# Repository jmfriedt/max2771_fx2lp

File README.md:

## MAX2771 multiband GNSS receiver for FX2LP

See [this movie](https://www.youtube.com/watch?v=B5UcFnkbXIk) to assess what the result of this
investigation might be. Many more GNSS bands and processing schemes are available with the very
flexible SDR reception platform. The use and results from the software in this repository
are featured in the French magazine <a href="https://connect.ed-diamond.com/hackable/hk-057/programmation-usb-sous-gnu-linux-application-du-fx2lp-pour-un-recepteur-de-radio-logicielle-dedie-aux-signaux-de-navigation-par-satellite-1-2">Hackable</a> (Nov-Dec 2024 and Mar-Apr 2025)

This project was featured on [Hackaday](https://hackaday.com/2024/11/03/gnss-reception-with-clone-sdr-board/)
November 3rd, 2024 and presented at the [2025 FOSDEM](https://www.fosdem.org/2025/schedule/event/fosdem-2025-4150-broadband-data-transfer-over-usb-for-gnu-linux-1-2-ghz-l-band-sdr-receiver-dedicated-to-gnss-and-other-reception-interfacing-with-pocketsdr-gnu-radio-and-gnss-sdr/). The original PocketSDR
<a href="https://www.mdpi.com/2226-4310/12/7/620">has been used</a> for assessing the Lunar Augmented Navigation Service.

### Objective: multi-MAX2771 GNSS receiver with up to 44 MS/s bulk USB communication

... for
* multiband GNSS (or other L-band signal) acquisition and processing if a power combiner 
(e.g. MiniCircuits ZAPD-2DC+) is used to feed both chips with the signal coming from a 
single multiband antenna
* CRPA (Controlled Radiation Pattern Antenna) if each chip is fed from a different
antenna for spatial diversity
* applicable to any L-band communication systems sampled with 2-3 bit ADC (verified with
Iridium)

Assembled daughter board: the missing 24 MHz oscillator is replaced with the 
24 MHz output from one of the resonator pins fitted on the FX2LP board. However,
the frequency pulling by the capacitor leads to a 3 kHz offset (2 ppm) which must
be compensated for when processing (acquisition phase of GNSS signal analysis) the
recorded signals. This feature is however illustrated to emphasize that the GNSS
receiver can be clocked by an external (24 MHz) source, a capability missing from most
commercial GNSS receivers.

Processing relies on the PocketSDR software provided by Tomoji Takasu at
https://github.com/tomojitakasu/PocketSDR.

The firmware for the FX2LP is compiled using opensource tools including the
``sdcc`` compiler, ``fx2lib`` library, ``cycfx2prog`` for prototyping the 8051 embedded
software and  ``fxload`` for flashing the onboard EEPROM.

### Getting started (assuming development on a GNU/Linux system)

1. Compile the FX2LP 8051 firmware (assumes ``sdcc`` is installed):
```
cd FX2LP/fx2lib
make
cd ../complete_fw
make
```
must complete with ``build/complete_fw.ihx`` in ``FX2LP/complete_fw``

2. Compile ``fxload`` for flashing the FX2LP
```
cd fxload
git submodule update --init
cmake .
make -j12
```

3. Flash the firmware in the FX2LP development board: switch on the board with the jumper to the bottom left (with the USB port facing
upward) closed in order to start the bootloader (``lsusb`` must return ``ID 04b4:8613 Cypress Semiconductor Corp. CY7C68013 EZ-USB FX2 
USB 2.0 Development Kit``):
```
sudo ./fxload/src/fxload load_eeprom --device 04b4:8613 --ihex-path ./FX2LP/complete_fw/build/complete_fw.ihx -t FX2LP --control-byte 0xC2 -s ./fxload/resources/Vend_Ax.hex
```
which must reply with
```
FX2:  config = 0x42, disconnected, I2C = 100 KHz
Done.
```

In case a message stating ``WARNING: don't see a large enough EEPROM`` is displayed, then the first byte of the EEPROM must be erased. To do so,
follow the sequences in ``FX2LP/bulk_read_example`` and most significantly the section about *Erase EEPROM and flash program to EEPROM*

4. Check the firmware has been flashed: switch off, remove the bottom-left jumper (to execute the firmware flashed in the EEPROM) and
restart the FX2LP: ``lsusb`` must now indicate ``ID 04b4:1004 Cypress Semiconductor Corp. There``

If so, the FX2LP is ready to communicate with PocketSDR ``app/pocket_conf/pocket_conf`` for configuring the MAX2771 (SPI communication)
or with ``app/pocket_dump/pocket_dump`` for streaming data from the FX2LP to the host computer through a USB Bulk interface.

## Cross compiling PocketSDR with Buildroot

Make sure FFTW with single precision resolution, and libusb are included 
in the Buildroot compilation toolchain.

0. in ``PocketSDR/lib/``: ``./clone_lib.sh`` as would be done on the host
1. in ``PocketSDR/lib/libfec``: 
```
./configure cross_compiling=yes --build=aarch64-buildroot-linux-gnu CC=aarch64-buildroot-linux-gnu-gcc
```
2. in ``PocketSDR/lib/build``, replace all ``CC = gcc`` in all .mk files with
``CC ?= gcc``, remove ``-DAVX2 -mavx2 -mfma`` from ``libsdr.mk``, and 
```
CC=aarch64-linux-gcc make
make install
```
3. in ``PocketSDR_RPi4/app``: edit all ``*/makefile`` and replace ``CC = g..``
with ``CC ?= g..`` (where .. is ``cc`` or ``++``), remove ``-DAVX2 -mavx2 -mfma``
from the ``pocket_snap`` makefile, and in ``makefile`` replace 
all ``make -C`` with ``CC=aarch64-linux-gcc make -C``
4. on a Raspberry Pi, make sure to increase CPU performance:
```
echo "performance" > /sys/devices/system/cpu/cpu0/cpufreq/scaling_governor
```
5. on a Raspberry Pi, make sure to write to a ramfs rather than the slow
SD card (``/tmp`` must be a tmpfs)

```
# ./app/pocket_dump/pocket_dump -t 10 /tmp/1.bin /tmp/2.bin
  TIME(s)    T   CH1(Bytes)   T   CH2(Bytes)   RATE(Ks/s)
     10.0   IQ     79953920  IQ     79953920       3995.3
# lsusb
Bus 001 Device 001: ID 1d6b:0002
Bus 001 Device 003: ID 04b4:1004
Bus 001 Device 002: ID 2109:3431
Bus 002 Device 001: ID 1d6b:0003
# uname -a
Linux buildroot 6.6.28-v8 #1 SMP PREEMPT Mon Feb  3 08:00:06 UTC 2025 aarch64 GNU/Linux
```
and the acqisition is validated on the host (the Raspberry Pi is lacking matplotlib and scipy)
with ``python3 python/pocket_acq.py -f 4  -sig L1CA -prn 1-32 /tmp/2.bin``

### Non-GNSS uses
The L-band is used for many non-GNSS applications. The VCO of the upper-L band receiver was tested
to lock up to 1638 MHz (RDIV=8, NDIV=546), well above Iridium (1616-1626.5 MHz), and down to 1458 MHz 
(RDIV=400, NDIV=24300), unfortunately still too high for the neutral hydrogen line (1420.4 MHz or 
38 MHz away, above the 22 MHz Nyquist frequency when sampling at 44 MS/s, the maximum rate allowed 
by the MAX2771) but compatible with <a href="https://www.youtube.com/watch?v=0UFHMCiM-60">Inmarsat</a>
(1525-1547 MHz).

The MAX2771 is expected to be compatible with receiving NISAR bursts since the 1257.5+/-40 MHz lies 
within the lower L-band VCO tuning range (1160-1290 MHz).

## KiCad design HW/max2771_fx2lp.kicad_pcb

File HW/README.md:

From Tomoji Takasu's Pocket SDR design, v2.3 found at https://github.com/tomojitakasu/PocketSDR, 
to be fitted on https://fr.aliexpress.com/item/1005006134347046.html FX2LP development board:

Schematic:

Notice that the low-pass matching filters L1/C2 and L3/C4 are fitted with 5.6 nH/1.7 pF and
8.4 nH/1.1 pF according to the typical application circuit found on page 49 of the datasheet.
The values are selected for the upper and lower L-band respectively. If both MAX2771 are to be
used in the same band, e.g. for CRPA, then replace the L/C values with the values best suited
for the targeted band.

Board layers (4-layer circuit to match the 50-ohm transmission lines in the L-band):

Use the interactive BOM (in the <a href="bom/">bom/</a> subdirectory) when assembling the board.

Result of the assembled board: configuring both MAX2771 to collect the 
upper (L1) band with 8 MHz sampling rate and 2 MHz IF bandwith
```
sudo ./app/pocket_conf/pocket_conf conf/pocket_L1L1_8MHz.conf
```
and recording using
```
sudo ./app/pocket_dump/pocket_dump -t 5 ch1.bin ch2.bin
```
The two binary files are processed for acquisition of GPS L1 C/A signal with
```
python3 ./python/pocket_acq.py ch2.bin -d 30000 -f 8 -fi 2 -sig L1CA -prn 1-32
```
with the ``-d`` option to reach Doppler shifts up to 30 kHz to account for
the poor quality TCXO whereas the default is to search for 5 kHz (theoretical
Doppler shift maximum assuming a perfect reference clock, e.g. Rb, Cs or HM 
source or good quality OCXO).

First demonstration, Doppler limited to 30 kHz offset from carrier:

Second demonstration, Doppler extended to 40 kHz offset from carrier matching the mobile phone
measurements:

Experimental setup:

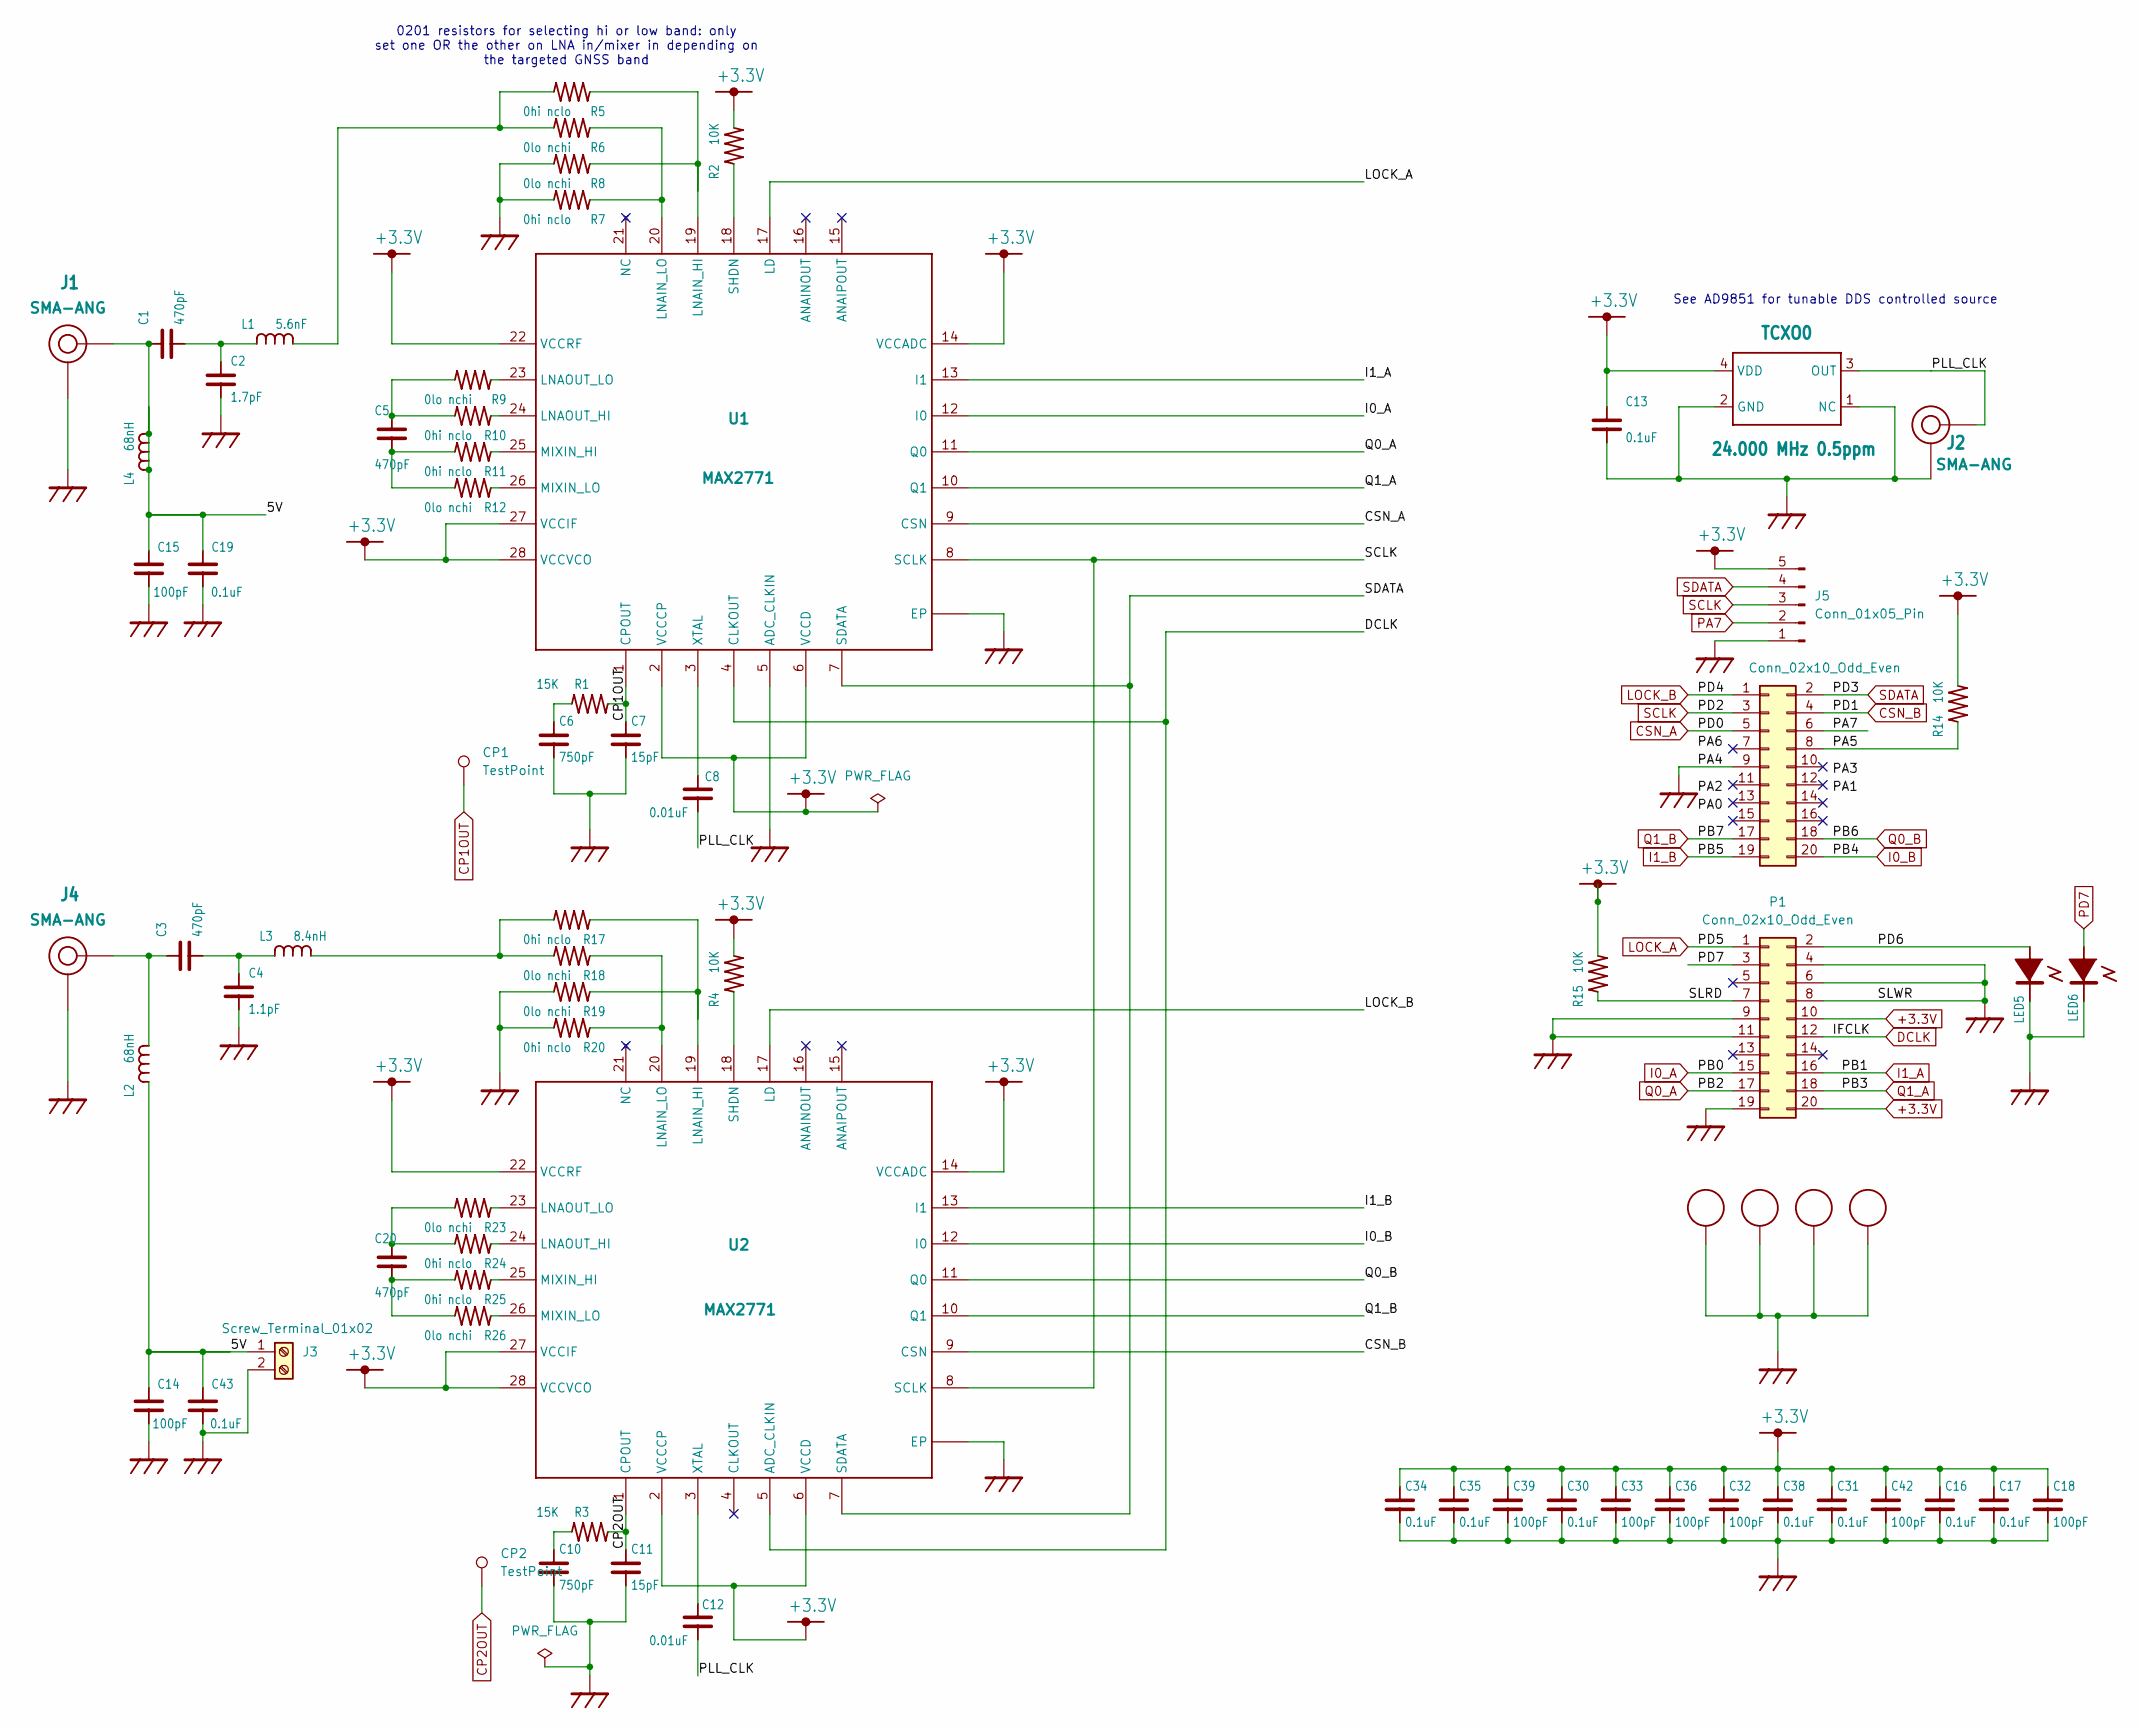
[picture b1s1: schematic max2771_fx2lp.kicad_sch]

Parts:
C1, C3, C5, C20: 470pF; C1005
C2: 1.7pF; C1005
C4: 1.1pF; C1005
C6, C10: 750pF; C1005
C7, C11: 15pF; C1005
C8, C12: 0.01uF; C1005
C13, C16, C17, C19, C30, C31, C34, C35, C38, C43: 0.1uF; C1005
C14, C15, C18, C32, C33, C36, C39, C42: 100pF; C1005
CP1, CP2: TestPoint; TestPoint_Pad_2.0x2.0mm
J1, J2, J4: SMA-ANG
J3: Screw_Terminal_01x02; PinHeader_1x02_P2.54mm_Vertical
J5: Conn_01x05_Pin; PinHeader_1x05_P2.54mm_Vertical
L1: 5.6nF; C1608
L2, L4: 68nH; C1608
L3: 8.4nH; C1608
LED5, LED6: LED1608; LED_1608
P1, P2: Conn_02x10_Odd_Even; PinSocket_2x10_P2.54mm_Vertical
R1, R3: 15K; C1005
R2, R4, R14, R15: 10K; C1005
R5, R7, R10, R11, R17, R20, R24, R25: 0hi nclo; R_0201_0603Metric
R6, R8, R9, R12, R18, R19, R23, R26: 0lo nchi; R_0201_0603Metric
TCXO0: 24.000 MHz 0.5ppm; TCXO
U1, U2: MAX2771; TQFN28

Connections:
+3.3V: C13.1, C16.1, C17.1, C18.1, C30.1, C31.1, C32.1, C33.1, C34.1, C35.1, C36.1, C38.1, C39.1, C42.1, J5.5, P1.10, P1.20, R2.2, R4.2, R14.2, R15.2, TCXO0.4 (VDD), U1.2 (VCCCP), U1.6 (VCCD), U1.14 (VCCADC), U1.22 (VCCRF), U1.27 (VCCIF), U1.28 (VCCVCO), U2.2 (VCCCP), U2.6 (VCCD), U2.14 (VCCADC), U2.22 (VCCRF), U2.27 (VCCIF), U2.28 (VCCVCO)
/PA5: P2.8, R14.1
/PD6: LED5.1 (+), P1.2
/PLL_CLK: C8.1, C12.1, J2.P1 (RF), TCXO0.3 (OUT)
/SLRD: P1.7, R15.1
CP1OUT: C7.1, CP1.1, R1.2, U1.1 (CPOUT)
CP2OUT: C11.1, CP2.1, R3.2, U2.1 (CPOUT)
CPAD_2.2MM: C2.1, C4.2, C6.2, C7.2, C10.2, C11.2, C13.2, C14.1, C15.1, C16.2, C17.2, C18.2, C19.1, C30.2, C31.2, C32.2, C33.2, C34.2, C35.2, C36.2, C38.2, C39.2, C42.2, C43.1, J1.P2 (GND), J1.P3 (GND), J1.P4 (GND), J1.P5 (GND), J2.P2 (GND), J2.P3 (GND), J2.P4 (GND), J2.P5 (GND), J3.2, J4.P2 (GND), J4.P3 (GND), J4.P4 (GND), J4.P5 (GND), J5.1, LED5.2, LED6.2, P1.4, P1.6, P1.8, P1.9, P1.11, P1.19, P2.9, R7.2, R8.2, R19.2, R20.2, TCXO0.1 (NC), TCXO0.2 (GND), U1.5 (ADC_CLKIN), U1.C1 (EP), U1.C2 (EP), U1.C3 (EP), U1.C4 (EP), U1.EP, U1.V1 (EP), U1.V2 (EP), U1.V3 (EP), U1.V4 (EP), U1.V5 (EP), U1.V6 (EP), U1.V7 (EP), U1.V8 (EP), U1.V9 (EP), U2.C1 (EP), U2.C2 (EP), U2.C3 (EP), U2.C4 (EP), U2.EP, U2.V1 (EP), U2.V2 (EP), U2.V3 (EP), U2.V4 (EP), U2.V5 (EP), U2.V6 (EP), U2.V7 (EP), U2.V8 (EP), U2.V9 (EP)
CSN_A: P2.5, U1.9 (CSN)
CSN_B: P2.4, U2.9 (CSN)
DCLK: P1.12, U1.4 (CLKOUT), U2.5 (ADC_CLKIN)
I0_A: P1.15, U1.12 (I0)
I0_B: P2.20, U2.12 (I0)
I1_A: P1.16, U1.13 (I1)
I1_B: P2.19, U2.13 (I1)
LOCK_A: P1.1, U1.17 (LD)
LOCK_B: P2.1, U2.17 (LD)
unnamed: C3.1, J4.P1 (RF), L2.2
unnamed: C1.2, C2.2, L1.1
unnamed: L1.2, R5.2, R6.2
unnamed: C3.2, C4.1, L3.1
unnamed: L3.2, R17.2, R18.2
unnamed: C6.1, R1.1
unnamed: R2.1, U1.18 (SHDN)
unnamed: C10.1, R3.1
unnamed: R4.1, U2.18 (SHDN)
unnamed: R5.1, R8.1, U1.19 (LNAIN_HI)
unnamed: R6.1, R7.1, U1.20 (LNAIN_LO)
unnamed: R9.1, U1.23 (LNAOUT_LO)
unnamed: R10.1, U1.24 (LNAOUT_HI)
unnamed: C5.1, R9.2, R10.2
unnamed: R11.1, U1.25 (MIXIN_HI)
unnamed: C5.2, R11.2, R12.2
unnamed: R12.1, U1.26 (MIXIN_LO)
unnamed: R17.1, R19.1, U2.19 (LNAIN_HI)
unnamed: R18.1, R20.1, U2.20 (LNAIN_LO)
unnamed: R23.1, U2.23 (LNAOUT_LO)
unnamed: C20.1, R23.2, R24.2
unnamed: R24.1, U2.24 (LNAOUT_HI)
unnamed: R25.1, U2.25 (MIXIN_HI)
unnamed: C20.2, R25.2, R26.2
unnamed: R26.1, U2.26 (MIXIN_LO)
unnamed: C8.2, U1.3 (XTAL)
unnamed: C12.2, U2.3 (XTAL)
PA7: J5.2, P2.6
PD7: LED6.1 (+), P1.3
Q0_A: P1.17, U1.11 (Q0)
Q0_B: P2.18, U2.11 (Q0)
Q1_A: P1.18, U1.10 (Q1)
Q1_B: P2.17, U2.10 (Q1)
SCLK: J5.3, P2.3, U1.8 (SCLK), U2.8 (SCLK)
SDATA: J5.4, P2.2, U1.7 (SDATA), U2.7 (SDATA)

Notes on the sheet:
0201 resistors for selecting hi or low band: only set one OR the other on LNA in/mixer in depending on the targeted GNSS band
See AD9851 for tunable DDS controlled source

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
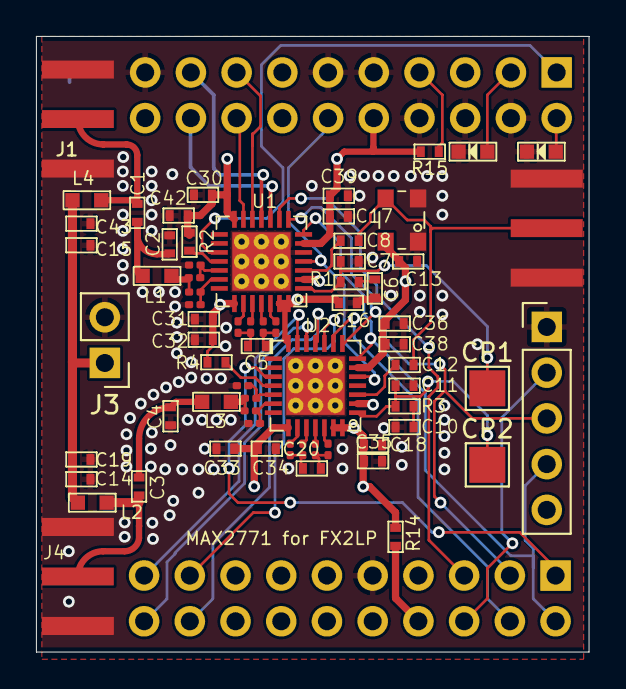
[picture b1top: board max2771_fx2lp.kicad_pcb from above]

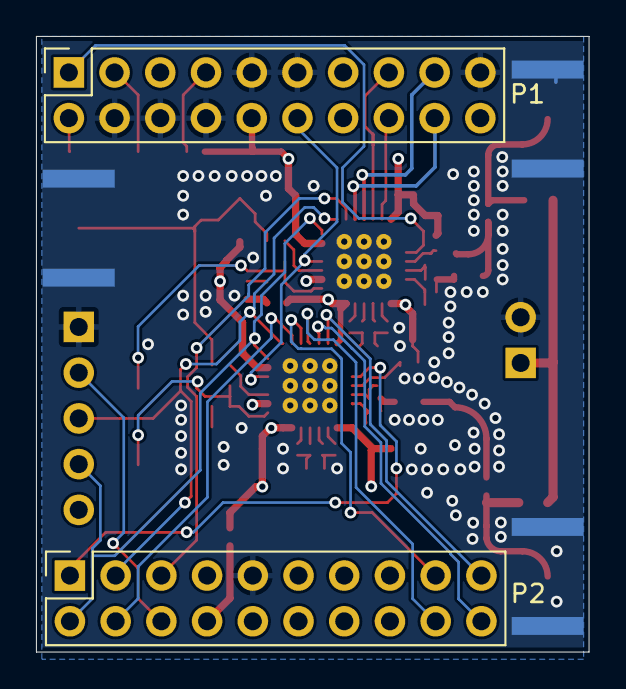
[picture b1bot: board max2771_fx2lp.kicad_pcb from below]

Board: 4 copper layers, 30.7 x 34.2 mm, 70 parts (2 on the bottom side), 54 nets.

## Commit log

2024-06-12 phone screenshot width
2024-06-13 add option for feeding either Hi or Lo frequency band
2024-06-13 sample data
2024-06-13 datasets + SVG
2024-06-14 mirror connectors
2024-06-15 final version sent for fabrication
2024-06-15 iridium band
2024-06-16 iridium signals + GPS squared carriers
2024-06-16 layout
2024-06-16 iridium decoding with gr-iridium
2024-06-16 finalized Iridium with IF
2024-06-22 README under MAX2771 Eval Board
2024-06-30 picture of the assembled board
2024-06-30 blinking LED example
2024-06-30 functional reception demonstration
2024-06-30 more functional example demo, increasedDoppler
2024-07-07 CRPA synchronization and gnss-sdr decoding
2024-07-07 spoofing description
2024-07-07 spoofing: genuine
2024-07-07 more gnss-sdr
2024-07-07 RINEX gnss-sdr
2024-07-09 python access to Vendor requests from PocketSDR firmware
2024-07-10 read/write MAX2771 registers from Python
2024-07-10 basic sdcc/fx2lib example handling Vendor Request messages with SPI bitbang emulation
2024-07-10 SPI management using sdcc and Vendor Request commands
2024-07-11 hardware validation procedure
2024-07-14 Keil vs SDCC endianness issue solved + final firmware with bulk USB communication
2024-07-14 README
2024-07-14 add EEPROM support
2024-07-14 datasheet: register layout
2024-07-14 ADC datarate
2024-07-15 Manually filled buffer bulk transfer example
2024-07-16 bulk transfer example in plain C
2024-07-17 Bulk USB interface read from C and Python, including from EEPROM
2024-07-17 EEPROM jumper
2024-07-29 real time processing and time offset exrtaction
2024-07-29 Allan deviation
2024-07-29 Allan deviation: README
2024-07-29 AD9851: README
2024-07-31 long term dt measurements
2024-07-31 time evolution
2024-08-04 add frequency offset
2024-08-05 first attempt at closed loop analysis
2024-08-05 add dataset
2024-08-06 update documentation/Makefile
2024-08-06 add test program
2024-08-12 AD9851 configuration script
2024-08-14 early init of AD9851
2024-08-19 GPSDO stability
2024-08-19 iridium
2024-08-19 first AD9851 tests
2024-10-05 repeat GPS spoofing detection with dual MAX2771 board
2024-10-21 enable EEPROM read/write
2024-10-21 correct error on eeprom write function
2024-10-21 add safety on EEPROM write
2024-10-21 add python test
2024-10-22 add datasheet reference
2024-10-22 mandatory pin configurations
2024-10-23 check bulk commuication with square wave clock generator
2024-10-23 add vendor request format
2024-10-24 Vendor Request format and handling
2024-10-24 LED polarity
2024-10-25 update READMEs
2024-10-26 move figure
2024-11-04 add translation of Hackable article
2024-11-05 update English translation of Hackable article
2024-12-31 add second article in English
2025-01-04 configuration files for RINEX differences
2025-01-04 Channels
2025-01-04 remove unnecessary config line
2025-01-08 RINEX pseudo-range difference
2025-01-08 fine delay measurement
2025-01-09 delay difference measurement
2025-01-09 update register 0 and register1 default values
2025-01-11 complex baseband measurements
2025-01-18 change VID/PID to allow multiple boards to be used simultaneously
2025-01-18 document pocket_scan usage
2025-01-25 real time display in GNU Radio
2025-01-31 decode packed 8 bits with GNU Radio
2025-02-07 update spoofing detection
2025-02-14 remove
2025-03-04 demonstrate L5 and E5 decoding in addition to E1 and L1
2025-03-07 rename E5 as E5a only
2025-03-27 test for IQ sign
2025-06-03 Starlink signal reception
2025-06-03 Starlink conf file
2025-06-11 passive bistatic radar
2025-06-17 phase analysis
2025-06-18 crop figures
2025-06-18 temperature measurements
2025-10-12 251012
2025-10-17 missing figure
2025-10-17 update figure
2025-10-26 add SMA 3D model
2025-10-26 add USB reset to allow multiple executions
2025-10-26 add GPIO control vendor request
2025-10-26 change device description
2025-11-15 update BOM
2025-11-16 new hardware
2025-11-16 update 3D view to move pin 1 of MAX2771 to the right position
2025-12-20 verification procedure and scripts
2026-01-04 image
2026-01-04 update verification sequence
2026-01-04 picture
2026-01-30 add SNR simulation
2026-02-19 E1 and E5 simultaneously
2026-02-20 throttled file sources
2026-02-20 update processing of E1/E5
2026-02-24 replace two File Sources with Multichannel_File_Signal_Source
2026-02-24 correct E1E5 script
2026-02-25 as many processing chains as files
